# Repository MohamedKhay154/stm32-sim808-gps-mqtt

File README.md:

# GPS Tracker Using STM32 and SIM808

Embedded IoT tracker based on STM32 and SIM808, providing
GPS positioning, SMS control, and MQTT communication with
a Node-RED backend.

## Features
- GPS position acquisition (SIM808)
- SMS send / receive
- MQTT communication over GPRS
- Node-RED dashboard integration
- Custom PCB design

## Repository Structure
stm32-sim808-gps-mqtt/

├── firmware/     STM32CubeIDE project

├── PCB Design/   PCB schematics and layout

├── Node-Red/     Node-RED flows and dashboard

├── Docs/         Documentation

├── Images/       Pictures

## System Overview

The STM32 communicates with the SIM808 module via UART.
GPS data is parsed on the MCU and sent either via SMS or
published to an MQTT broker over GPRS. Node-RED processes
incoming data and provides visualization and control.

## PCB Design

The PCB design is divided into two separate boards:

1.One board for the STM32 MCU

2.One board for the SIM808 module

These boards are stacked on top of each other using a common connector interface.

# SIM808 

Notes:

The board uses a LiPo battery as the main power source. The SIM808 module includes an internal charging circuit accessible via USB.

According to the datasheet, when powering the system with a LiPo battery, no additional voltage regulator is needed, provided the battery delivers 3.7 V nominal and 2 A peak.

Both the GPS and GSM antennas require 50 Ω impedance traces and should be placed as close as possible to the module for optimal signal performance.

# STM32 

Notes:

The board uses an MCP1700 voltage regulator to provide stable 3.3 V to the STM32.

There are two power inputs:

1.USB

2.Power from the SIM808 board via a dedicated connector

A Schottky diode is used to prevent backflow and protect the STM32 when multiple power sources are connected.

## Firmware Design

The firmware is structured around a finite state machine (FSM) to securely manage the different operational modes of the module:

- Idle: The module waits for incoming commands or triggers.

- Tracking: Begins continuous position tracking using a timer.

- Parking: Sends the current position and waits for either a “theft move” or “stop” command.

- Reconnect: At any state, if the module detects a disconnection, it transitions to the Reconnect state to re-establish the connection, then returns to the previous state.

Alongside the FSM, a watchdog timer monitors the connection every 30 seconds and attempts to reconnect if needed, ensuring reliable communication.

# Firmware Modules

* SIM808.c
Responsible for all SIM808 communications, including:

- Sending AT commands

- Parsing GPS data

- Handling message transmission and waiting for responses

* MQTT (mqtt.c / mqtt.h)
Implements the MQTT protocol using the Paho MQTT library, helping to build and send MQTT packets.

* tracker_fsm.c
Implements the state machine, including:

- Event handlers
- State transitions

## Node-RED Dashboard

The dashboard is built using Node-RED and a world map visualization.

Node-RED natively supports MQTT, so once the STM32 firmware publishes a position, the Node-RED flow (as a subscriber) receives it and displays it as a pointer on the map.

Since the system has multiple operational modes (continuous tracking, parking, etc.), a global variable tracks the current mode. This allows the dashboard to adjust the visualization accordingly:

Continuous tracking → plots the path as a line

Parking mode → shows a circle around the parked area

Commands are sent from the dashboard using buttons that publish messages to the MQTT broker. The SIM808 module on the device subscribes to these commands and acts accordingly.

## Further Notes

The project is still under development.

The source code is being updated and may change as new features are added or improvements are made.

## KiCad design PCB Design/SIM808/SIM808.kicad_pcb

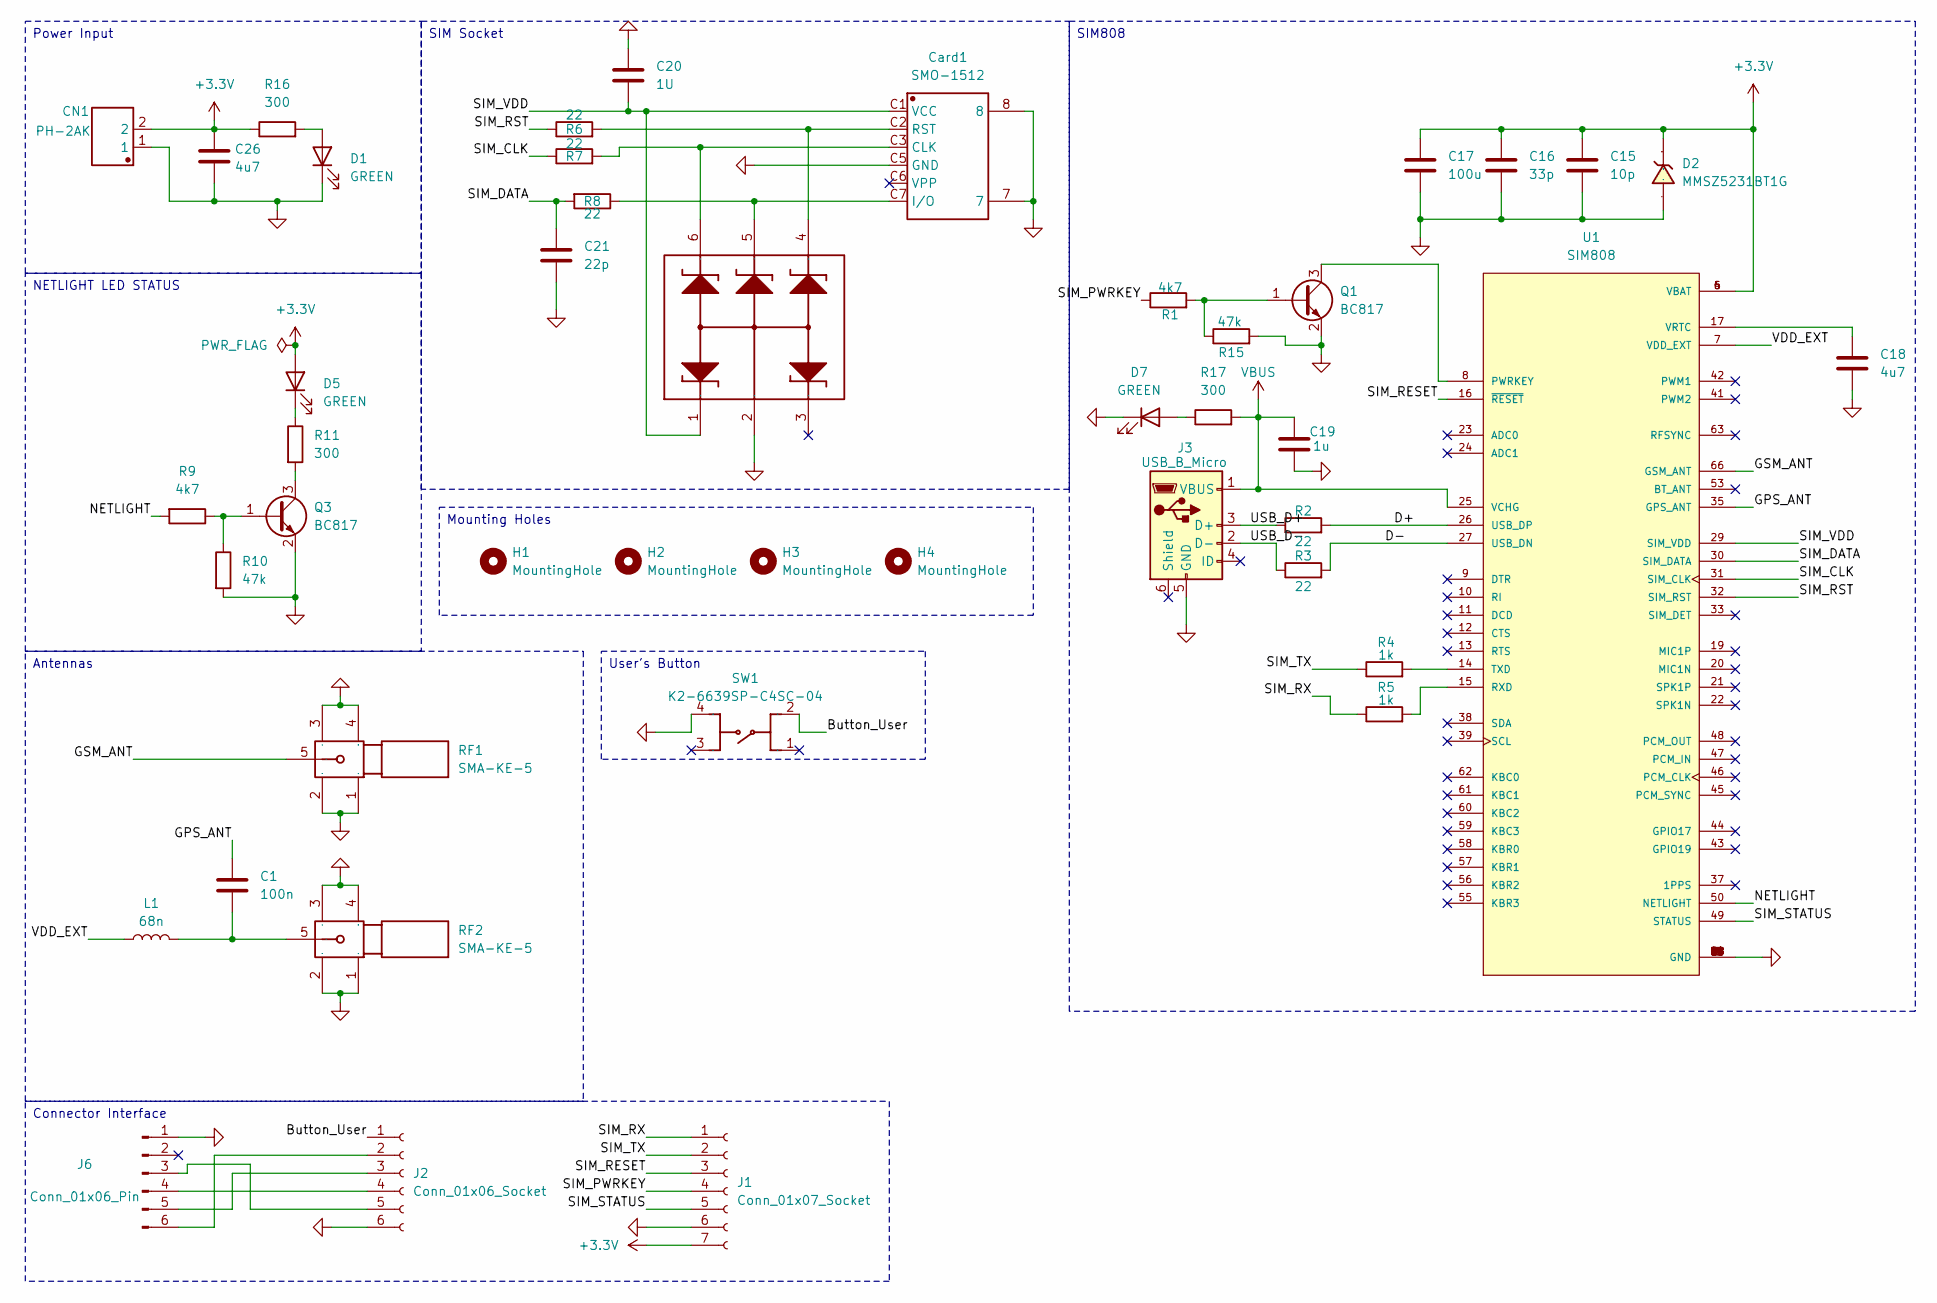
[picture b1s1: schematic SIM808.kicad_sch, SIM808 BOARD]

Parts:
C1: 100n; C_0402_1005Metric
C15: 10p; C_0603_1608Metric
C16: 33p; C_0603_1608Metric
C17: 100u; C_0805_2012Metric
C18, C26: 4u7; C_0805_2012Metric
C19: 1u; C_0805_2012Metric
C20: 1U; C_0805_2012Metric
C21: 22p; C_0603_1608Metric
CN1: PH-2AK; CONN-TH_PH-2A; Manufacturer Part PH-2AK
Card1: SMO-1512; SIM_SMD_SMO_1512; Manufacturer Part SMO-1512
D1, D5, D7: GREEN; LED_0201_0603Metric
D2: MMSZ5231BT1G; SOD-123_L2.8-W1.8-LS3.7-RD; Manufacturer Part MMSZ5231BT1G
D3: SMF12CT1G; Manufacturer Part SMF12CT1G
H1, H2, H3, H4: MountingHole; MountingHole_2.2mm_M2
J1: Conn_01x07_Socket; PinSocket_1x07_P2.54mm_Vertical
J2: Conn_01x06_Socket; PinSocket_1x06_P2.54mm_Vertical
J3: USB_B_Micro; USB_Micro-B_Wuerth_629105150521
J6: Conn_01x06_Pin; PinHeader_1x06_P2.54mm_Vertical
L1: 68n; L_0402_1005Metric
Q1, Q3: BC817; SOT-23
R1, R9: 4k7; R_0805_2012Metric
R2, R3, R6, R7, R8: 22; R_0603_1608Metric
R4, R5: 1k; R_0805_2012Metric
R10, R15: 47k; R_0805_2012Metric
R11, R16, R17: 300; R_0603_1608Metric
RF1, RF2: SMA-KE-5; SMA-TH_SMA-KE-5; Manufacturer Part SMA-KE-5
SW1: K2-6639SP-C4SC-04; KEY-SMD_4P-L6.0-W6.0-P3.90-LS9.0; Manufacturer Part K2-6639SP-C4SC-04
U1: SIM808; XCVR_SIM808; PARTREV 1.03

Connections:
+3.3V: C15.2, C16.2, C17.2, C26.2, CN1.2, D2.1 (K), D5.2 (A), J1.7, R16.1, U1.4 (VBAT), U1.5 (VBAT), U1.6 (VBAT)
/Button_User: J2.1, SW1.2
/D+: R2.2, U1.26 (USB_DP)
/D-: R3.2, U1.27 (USB_DN)
/GPS_ANT: C1.1, U1.35 (GPS_ANT)
/GSM_ANT: RF1.5, U1.66 (GSM_ANT)
/NETLIGHT: R9.2, U1.50 (NETLIGHT)
/SIM_CLK: R7.1, U1.31 (SIM_CLK)
/SIM_DATA: C21.1, R8.2, U1.30 (SIM_DATA)
/SIM_PWRKEY: J1.4, R1.1
/SIM_RESET: J1.3, U1.16 (~RESET)
/SIM_RST: R6.1, U1.32 (SIM_RST)
/SIM_RX: J1.1, R5.1
/SIM_STATUS: J1.5, U1.49 (STATUS)
/SIM_TX: J1.2, R4.1
/SIM_VDD: C20.2, Card1.C1 (VCC), D3.1, U1.29 (SIM_VDD)
/USB_D+: J3.3 (D+), R2.1
/USB_D-: J3.2 (D-), R3.1
/VDD_EXT: L1.1, U1.7 (VDD_EXT)
GND: C15.1, C16.1, C17.1, C18.1, C19.1, C20.1, C21.2, C26.1, CN1.1, Card1.7, Card1.8, Card1.C5 (GND), D1.1 (K), D2.2 (A), D3.2, D7.1 (K), J1.6, J2.6, J3.5 (GND), J6.1, Q1.2 (E), Q3.2 (E), R10.2, R15.2, RF1.1, RF1.2, RF1.3, RF1.4, RF2.1, RF2.2, RF2.3, RF2.4, SW1.4, U1.1 (GND), U1.2 (GND), U1.3 (GND), U1.18 (GND), U1.28 (GND), U1.34 (GND), U1.36 (GND), U1.40 (GND), U1.51 (GND), U1.52 (GND), U1.54 (GND), U1.64 (GND), U1.65 (GND), U1.67 (GND), U1.68 (GND)
unnamed: C1.2, L1.2, RF2.5
unnamed: Card1.C3 (CLK), D3.6, R7.2
unnamed: Card1.C7 (I/O), D3.5, R8.1
unnamed: Card1.C2 (RST), D3.4, R6.2
unnamed: D1.2 (A), R16.2
unnamed: D5.1 (K), R11.1
unnamed: D7.2 (A), R17.1
unnamed: J2.2, J6.6
unnamed: J2.3, J6.5
unnamed: J2.4, J6.4
unnamed: J2.5, J6.3
unnamed: Q1.1 (B), R1.2, R15.1
unnamed: Q1.3 (C), U1.8 (PWRKEY)
unnamed: Q3.1 (B), R9.1, R10.1
unnamed: Q3.3 (C), R11.2
unnamed: R5.2, U1.15 (RXD)
unnamed: R4.2, U1.14 (TXD)
unnamed: C18.2, U1.17 (VRTC)
VBUS: C19.2, J3.1 (VBUS), R17.2, U1.25 (VCHG)

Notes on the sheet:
User's Button
Mounting Holes
NETLIGHT LED STATUS
Connector Interface
Power Input
Antennas
SIM808
SIM Socket

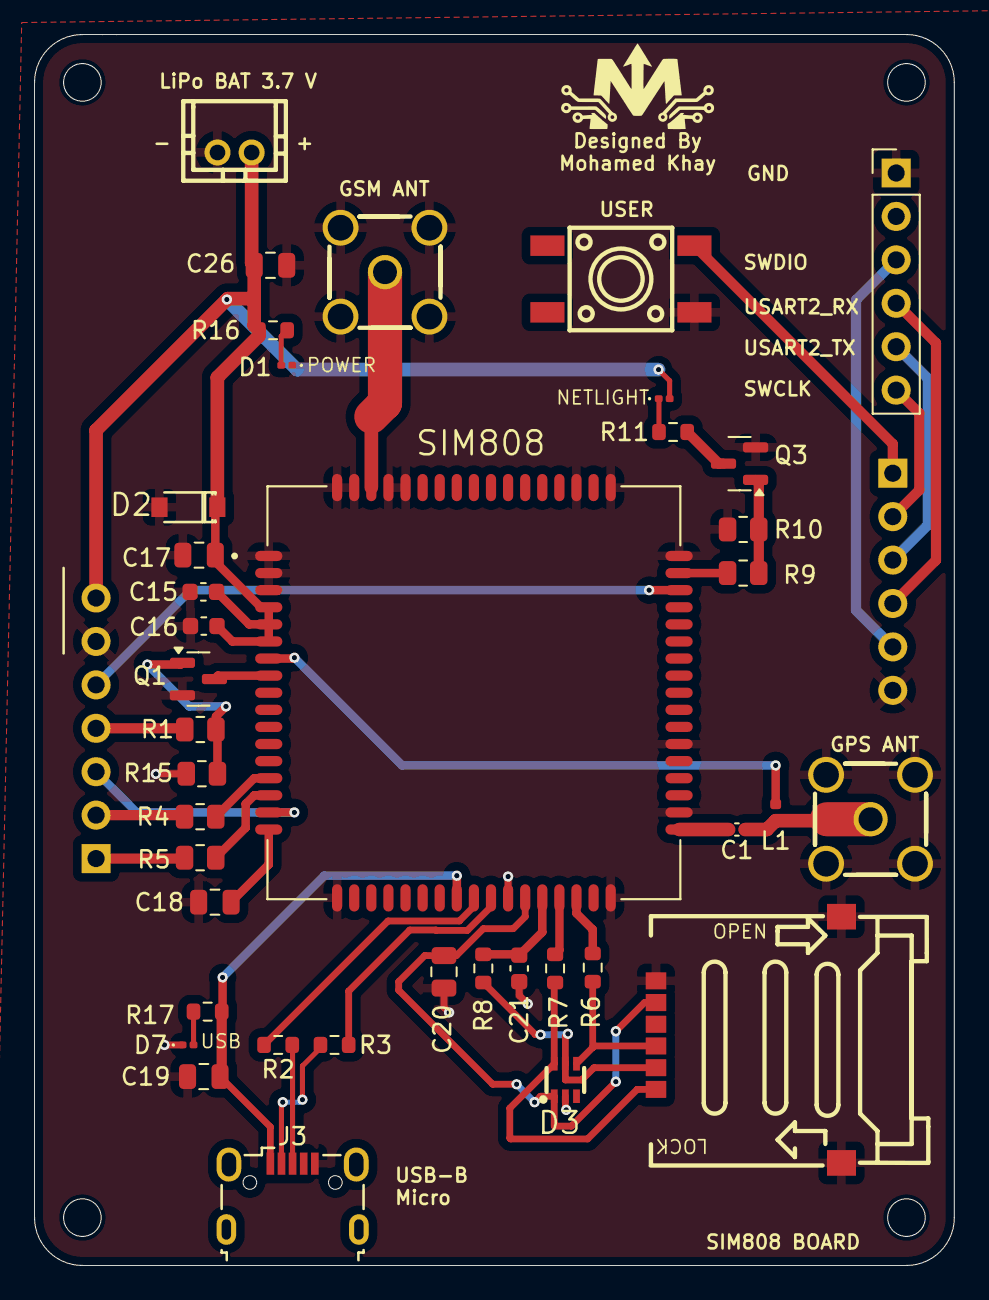
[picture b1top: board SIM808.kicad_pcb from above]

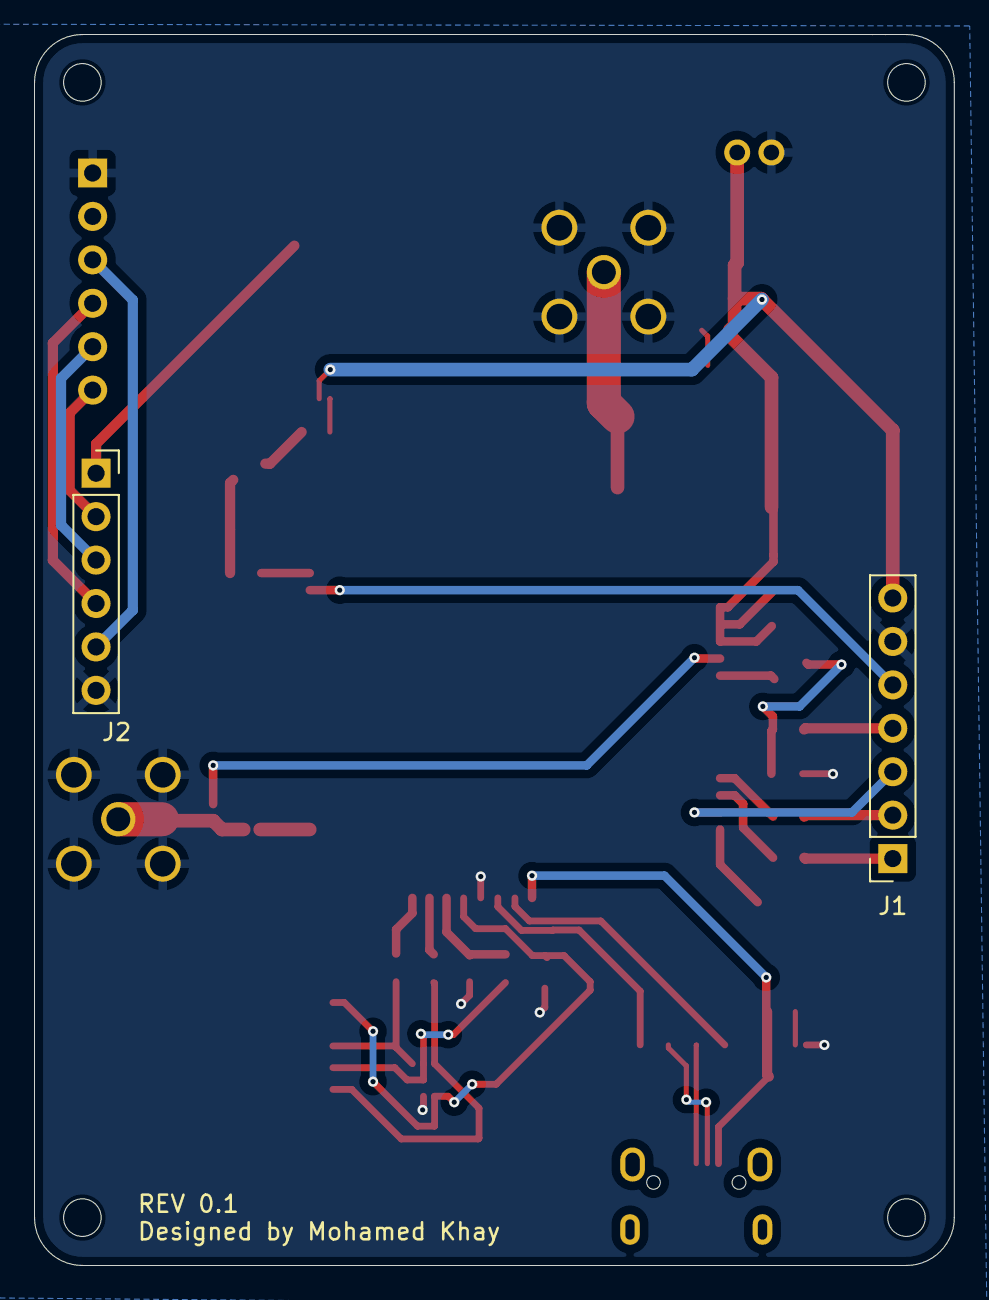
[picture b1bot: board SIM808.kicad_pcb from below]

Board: 2 copper layers, 53.8 x 72.0 mm, 45 parts (2 on the bottom side), 39 nets.

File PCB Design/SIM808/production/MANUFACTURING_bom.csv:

Designator,Footprint,Quantity,Value,LCSC Part #
C1,0402,1,100n,
C15,0603,1,10p,
C16,0603,1,33p,
C17,0805,1,100u,
"C18, C26",0805,2,4u7,
"C19, C20",0805,2,1u,
C21,0603,1,22p,
CARD1,SIM_SMD_SMO_1512,1,SMO-1512,
CN1,CONN-TH_PH-2A,1,PH-2AK,
"D1, D5, D7",0201,3,GREEN,
D2,SOD-123_L2.8-W1.8-LS3.7-RD,1,MMSZ5231BT1G,
D3,SMF12CT1G,1,SMF12CT1G,
J1,PinSocket_1x07_P2.54mm_Vertical,1,Conn_01x07_Socket,
J2,PinSocket_1x06_P2.54mm_Vertical,1,Conn_01x06_Socket,
J3,USB_Micro-B_Wuerth_629105150521,1,USB_B_Micro,
J6,PinHeader_1x06_P2.54mm_Vertical,1,Conn_01x06_Pin,
L1,0402,1,68n,
"Q1, Q3",SOT-23,2,BC817,
"R1, R9",0805,2,4k7,
"R10, R15",0805,2,47k,
"R11, R16, R17",0603,3,300,
"R2, R3, R6, R7, R8",0603,5,22,
"R4, R5",0805,2,1k,
"RF1, RF2",SMA-TH_SMA-KE-5,2,SMA-KE-5,
SW1,KEY-SMD_4P-L6.0-W6.0-P3.90-LS9.0,1,K2-6639SP-C4SC-04,
U1,XCVR_SIM808,1,SIM808,

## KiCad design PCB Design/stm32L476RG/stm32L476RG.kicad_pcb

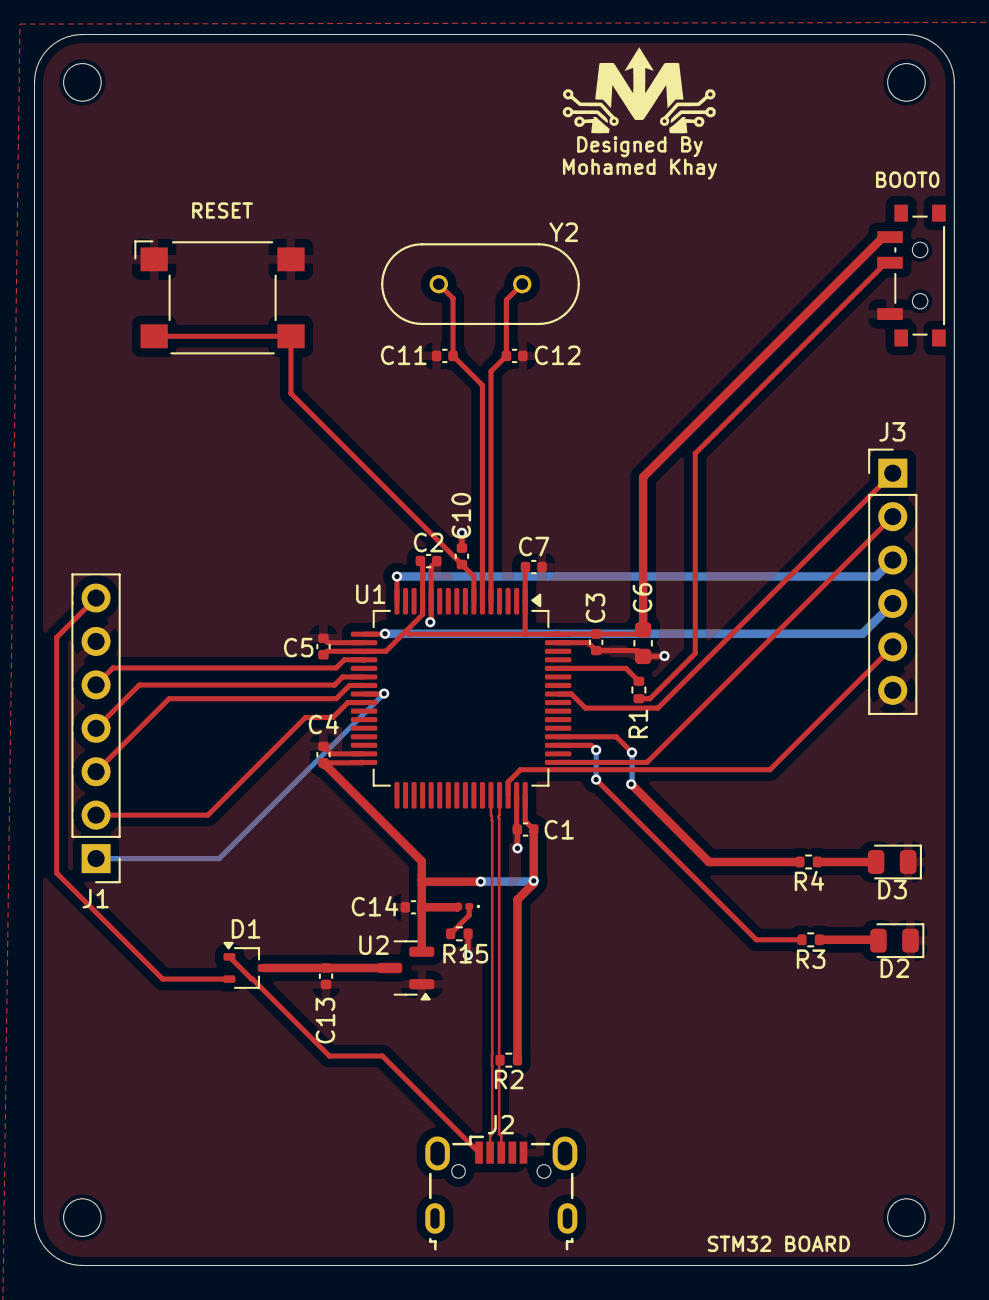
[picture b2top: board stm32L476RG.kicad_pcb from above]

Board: 2 copper layers, 53.8 x 72.0 mm, 33 parts (0 on the bottom side), 27 nets.

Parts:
C1, C2, C3, C4, C5, C7, C10: 100n; C_0402_1005Metric
C6: 10u; C_0603_1608Metric
C11, C12: 15p; C_0402_1005Metric
C13, C14: 1u; C_0402_1005Metric
D1: BAT54CW; SOT-323_SC-70
D2: RED; LED_0805_2012Metric
D3: GREEN; LED_0805_2012Metric
D6: RED; LED_0201_0603Metric
H1, H2, H3, H4: MountingHole; MountingHole_2.2mm_M2
J1: Conn_01x07_Pin; PinHeader_1x07_P2.54mm_Vertical
J2: USB_B_Micro; USB_Micro-B_Wuerth_629105150521
J3: Conn_01x06_Pin; PinHeader_1x06_P2.54mm_Vertical
R1: 10k; R_0402_1005Metric
R2, R3, R4, R15: 1k5; R_0402_1005Metric
SW1: SW_SPDT; SW_SPDT_PCM12_NO_TIP
SW2: SW_Omron_B3FS; SW_SPST_Omron_B3FS-100xP
U1: STM32L476RGTx; LQFP-64_10x10mm_P0.5mm
U2: MCP1700x-330xxTT; SOT-23
Y2: 48M; XTAL_HC49P488W43L1150T466H350

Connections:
+3.3V: C1.1, C2.1, C3.1, C4.1, C5.1, C6.1, C7.1, C14.1, D6.2 (A), R2.1, SW1.3 (C), U1.1 (VBAT), U1.13 (VDDA), U1.19 (VDD), U1.32 (VDD), U1.48 (VDDUSB), U1.64 (VDD), U2.2 (VO)
/BOOT0: R1.2, U1.60 (BOOT0)
/Button_User: J3.1, U1.57 (PB5)
/D+: J2.3 (D+), R2.2, U1.45 (PA12)
/D-: J2.2 (D-), U1.44 (PA11)
/NRST: C10.1, SW2.2, U1.7 (NRST)
/RCC_IN: C12.1, U1.5 (PH0), Y2.1
/RCC_OUT: C11.1, U1.6 (PH1), Y2.2
/SIM_PWRKEY: J1.4, U1.22 (PA6)
/SIM_RESET: J1.3, U1.23 (PA7)
/SIM_RX: J1.1, U1.24 (PC4)
/SIM_STATUS: J1.5, U1.20 (PA4)
/SIM_TX: J1.2, U1.25 (PC5)
/SWCLK: J3.2, U1.49 (PA14)
/SWDIO: J3.5, U1.46 (PA13)
/SW_BOOT0: R1.1, SW1.2 (B)
/SYS_PWR_IN: D1.2, J1.7
/USART2_RX: J3.4, U1.17 (PA3)
/USART2_TX: J3.3, U1.16 (PA2)
GND: C1.2, C2.2, C3.2, C4.2, C5.2, C6.2, C7.2, C10.2, C11.2, C12.2, C13.2, C14.2, D2.1 (K), D3.1 (K), J1.6, J2.5 (GND), J3.6, R15.2, SW1.1 (A), SW2.1, U1.12 (VSSA), U1.18 (VSS), U1.31 (VSS), U1.47 (VSS), U1.63 (VSS), U2.1 (GND)
unnamed: D2.2 (A), R3.1
unnamed: D3.2 (A), R4.1
unnamed: D6.1 (K), R15.1
unnamed: R3.2, U1.51 (PC10)
unnamed: R4.2, U1.52 (PC11)
unnamed: C13.1, D1.3, U2.3 (VI)
VBUS: D1.1, J2.1 (VBUS)

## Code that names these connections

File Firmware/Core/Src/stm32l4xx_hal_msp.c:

/* USER CODE BEGIN Header */
/**
  ******************************************************************************
  * @file         stm32l4xx_hal_msp.c
  * @brief        This file provides code for the MSP Initialization
  *               and de-Initialization codes.
  ******************************************************************************
  * @attention
  *
  * Copyright (c) 2025 STMicroelectronics.
  * All rights reserved.
  *
  * This software is licensed under terms that can be found in the LICENSE file
  * in the root directory of this software component.
  * If no LICENSE file comes with this software, it is provided AS-IS.
  *
  ******************************************************************************
  */
/* USER CODE END Header */

/* Includes ------------------------------------------------------------------*/
#include "main.h"
/* USER CODE BEGIN Includes */

/* USER CODE END Includes */

/* Private typedef -----------------------------------------------------------*/
/* USER CODE BEGIN TD */

/* USER CODE END TD */

/* Private define ------------------------------------------------------------*/
/* USER CODE BEGIN Define */

/* USER CODE END Define */

/* Private macro -------------------------------------------------------------*/
/* USER CODE BEGIN Macro */

/* USER CODE END Macro */

/* Private variables ---------------------------------------------------------*/
/* USER CODE BEGIN PV */

/* USER CODE END PV */

/* Private function prototypes -----------------------------------------------*/
/* USER CODE BEGIN PFP */

/* USER CODE END PFP */

/* External functions --------------------------------------------------------*/
/* USER CODE BEGIN ExternalFunctions */

/* USER CODE END ExternalFunctions */

/* USER CODE BEGIN 0 */

/* USER CODE END 0 */
/**
  * Initializes the Global MSP.
  */
void HAL_MspInit(void)
{

  /* USER CODE BEGIN MspInit 0 */

  /* USER CODE END MspInit 0 */

  __HAL_RCC_SYSCFG_CLK_ENABLE();
  __HAL_RCC_PWR_CLK_ENABLE();

  /* System interrupt init*/

  /* USER CODE BEGIN MspInit 1 */

  /* USER CODE END MspInit 1 */
}

/**
* @brief TIM_Base MSP Initialization
* This function configures the hardware resources used in this example
* @param htim_base: TIM_Base handle pointer
* @retval None
*/
void HAL_TIM_Base_MspInit(TIM_HandleTypeDef* htim_base)
{
  if(htim_base->Instance==TIM2)
  {
  /* USER CODE BEGIN TIM2_MspInit 0 */

  /* USER CODE END TIM2_MspInit 0 */
    /* Peripheral clock enable */
    __HAL_RCC_TIM2_CLK_ENABLE();
    /* TIM2 interrupt Init */
    HAL_NVIC_SetPriority(TIM2_IRQn, 0, 0);
    HAL_NVIC_EnableIRQ(TIM2_IRQn);
  /* USER CODE BEGIN TIM2_MspInit 1 */

  /* USER CODE END TIM2_MspInit 1 */
  }
  else if(htim_base->Instance==TIM3)
  {
  /* USER CODE BEGIN TIM3_MspInit 0 */

  /* USER CODE END TIM3_MspInit 0 */
    /* Peripheral clock enable */
    __HAL_RCC_TIM3_CLK_ENABLE();
    /* TIM3 interrupt Init */
    HAL_NVIC_SetPriority(TIM3_IRQn, 0, 0);
    HAL_NVIC_EnableIRQ(TIM3_IRQn);
  /* USER CODE BEGIN TIM3_MspInit 1 */

  /* USER CODE END TIM3_MspInit 1 */
  }

}

/**
* @brief TIM_Base MSP De-Initialization
* This function freeze the hardware resources used in this example
* @param htim_base: TIM_Base handle pointer
* @retval None
*/
void HAL_TIM_Base_MspDeInit(TIM_HandleTypeDef* htim_base)
{
  if(htim_base->Instance==TIM2)
  {
  /* USER CODE BEGIN TIM2_MspDeInit 0 */

  /* USER CODE END TIM2_MspDeInit 0 */
    /* Peripheral clock disable */
    __HAL_RCC_TIM2_CLK_DISABLE();

    /* TIM2 interrupt DeInit */
    HAL_NVIC_DisableIRQ(TIM2_IRQn);
  /* USER CODE BEGIN TIM2_MspDeInit 1 */

  /* USER CODE END TIM2_MspDeInit 1 */
  }
  else if(htim_base->Instance==TIM3)
  {
  /* USER CODE BEGIN TIM3_MspDeInit 0 */

  /* USER CODE END TIM3_MspDeInit 0 */
    /* Peripheral clock disable */
    __HAL_RCC_TIM3_CLK_DISABLE();

    /* TIM3 interrupt DeInit */
    HAL_NVIC_DisableIRQ(TIM3_IRQn);
  /* USER CODE BEGIN TIM3_MspDeInit 1 */

  /* USER CODE END TIM3_MspDeInit 1 */
  }

}

/**
* @brief UART MSP Initialization
* This function configures the hardware resources used in this example
* @param huart: UART handle pointer
* @retval None
*/
void HAL_UART_MspInit(UART_HandleTypeDef* huart)
{
  GPIO_InitTypeDef GPIO_InitStruct = {0};
  RCC_PeriphCLKInitTypeDef PeriphClkInit = {0};
  if(huart->Instance==USART2)
  {
  /* USER CODE BEGIN USART2_MspInit 0 */

  /* USER CODE END USART2_MspInit 0 */

  /** Initializes the peripherals clock
  */
    PeriphClkInit.PeriphClockSelection = RCC_PERIPHCLK_USART2;
    PeriphClkInit.Usart2ClockSelection = RCC_USART2CLKSOURCE_PCLK1;
    if (HAL_RCCEx_PeriphCLKConfig(&PeriphClkInit) != HAL_OK)
    {
      Error_Handler();
    }

    /* Peripheral clock enable */
    __HAL_RCC_USART2_CLK_ENABLE();

    __HAL_RCC_GPIOA_CLK_ENABLE();
    /**USART2 GPIO Configuration
    PA2     ------> USART2_TX
    PA3     ------> USART2_RX
    */
    GPIO_InitStruct.Pin = USART_TX_Pin|USART_RX_Pin;
    GPIO_InitStruct.Mode = GPIO_MODE_AF_PP;
    GPIO_InitStruct.Pull = GPIO_NOPULL;
    GPIO_InitStruct.Speed = GPIO_SPEED_FREQ_VERY_HIGH;
    GPIO_InitStruct.Alternate = GPIO_AF7_USART2;
    HAL_GPIO_Init(GPIOA, &GPIO_InitStruct);

  /* USER CODE BEGIN USART2_MspInit 1 */

  /* USER CODE END USART2_MspInit 1 */
  }
  else if(huart->Instance==USART3)
  {
  /* USER CODE BEGIN USART3_MspInit 0 */

  /* USER CODE END USART3_MspInit 0 */

  /** Initializes the peripherals clock
  */
    PeriphClkInit.PeriphClockSelection = RCC_PERIPHCLK_USART3;
    PeriphClkInit.Usart3ClockSelection = RCC_USART3CLKSOURCE_PCLK1;
    if (HAL_RCCEx_PeriphCLKConfig(&PeriphClkInit) != HAL_OK)
    {
      Error_Handler();
    }

    /* Peripheral clock enable */
    __HAL_RCC_USART3_CLK_ENABLE();

    __HAL_RCC_GPIOC_CLK_ENABLE();
    /**USART3 GPIO Configuration
    PC4     ------> USART3_TX
    PC5     ------> USART3_RX
    */
    GPIO_InitStruct.Pin = GPIO_PIN_4|GPIO_PIN_5;
    GPIO_InitStruct.Mode = GPIO_MODE_AF_PP;
    GPIO_InitStruct.Pull = GPIO_NOPULL;
    GPIO_InitStruct.Speed = GPIO_SPEED_FREQ_VERY_HIGH;
    GPIO_InitStruct.Alternate = GPIO_AF7_USART3;
    HAL_GPIO_Init(GPIOC, &GPIO_InitStruct);

    /* USART3 interrupt Init */
    HAL_NVIC_SetPriority(USART3_IRQn, 0, 0);
    HAL_NVIC_EnableIRQ(USART3_IRQn);
  /* USER CODE BEGIN USART3_MspInit 1 */

  /* USER CODE END USART3_MspInit 1 */
  }

}

/**
* @brief UART MSP De-Initialization
* This function freeze the hardware resources used in this example
* @param huart: UART handle pointer
* @retval None
*/
void HAL_UART_MspDeInit(UART_HandleTypeDef* huart)
{
  if(huart->Instance==USART2)
  {
  /* USER CODE BEGIN USART2_MspDeInit 0 */

  /* USER CODE END USART2_MspDeInit 0 */
    /* Peripheral clock disable */
    __HAL_RCC_USART2_CLK_DISABLE();

    /**USART2 GPIO Configuration
    PA2     ------> USART2_TX
    PA3     ------> USART2_RX
    */
    HAL_GPIO_DeInit(GPIOA, USART_TX_Pin|USART_RX_Pin);

  /* USER CODE BEGIN USART2_MspDeInit 1 */

  /* USER CODE END USART2_MspDeInit 1 */
  }
  else if(huart->Instance==USART3)
  {
  /* USER CODE BEGIN USART3_MspDeInit 0 */

  /* USER CODE END USART3_MspDeInit 0 */
    /* Peripheral clock disable */
    __HAL_RCC_USART3_CLK_DISABLE();

    /**USART3 GPIO Configuration
    PC4     ------> USART3_TX
    PC5     ------> USART3_RX
    */
    HAL_GPIO_DeInit(GPIOC, GPIO_PIN_4|GPIO_PIN_5);

    /* USART3 interrupt DeInit */
    HAL_NVIC_DisableIRQ(USART3_IRQn);
  /* USER CODE BEGIN USART3_MspDeInit 1 */

  /* USER CODE END USART3_MspDeInit 1 */
  }

}

/* USER CODE BEGIN 1 */

/* USER CODE END 1 */

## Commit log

2026-01-17 edit
